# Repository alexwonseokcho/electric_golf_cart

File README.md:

# electric_golf_cart
Electric golf push cart made with hoverboard motors. Remote controlled with ESP-NOW, featuring an IMU-enabled autobalancing mode.

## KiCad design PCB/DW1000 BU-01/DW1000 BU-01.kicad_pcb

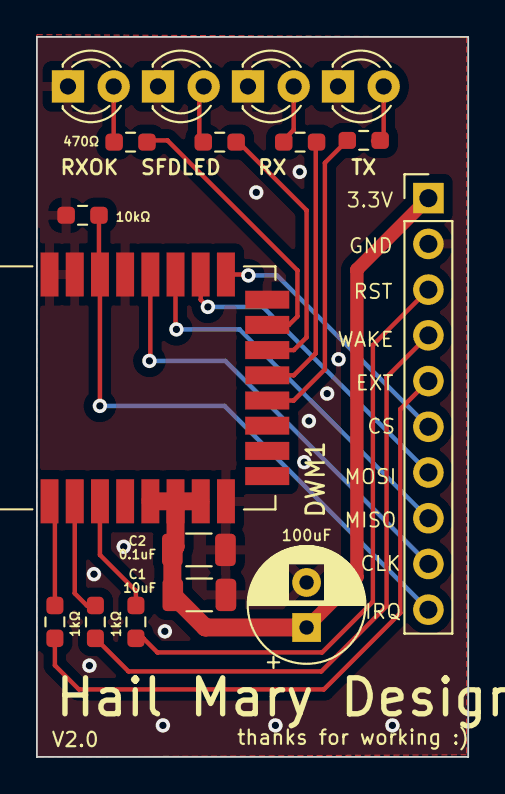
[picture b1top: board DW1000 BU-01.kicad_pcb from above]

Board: 2 copper layers, 24.0 x 40.0 mm, 17 parts (0 on the bottom side), 21 nets.

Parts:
C1: 10uF; C_1206_3216Metric
C2: 0.1uF; C_1206_3216Metric
C3: 100uF; CP_Radial_D6.3mm_P2.50mm
D1: RXOK; LED_D3.0mm
D2: SFDLED; LED_D3.0mm
D3: RX; LED_D3.0mm
D4: TX; LED_D3.0mm
DWM1: DWM1000
J1: Conn_01x10_Pin; PinHeader_1x10_P2.54mm_Vertical
R1, R2, R3, R4: R470; R_0603_1608Metric_Pad0.98x0.95mm_HandSolder
R5: R10k; R_0603_1608Metric_Pad0.98x0.95mm_HandSolder
R6, R7, R8: R1k; R_0603_1608Metric_Pad0.98x0.95mm_HandSolder

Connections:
+3.3V: C1.1, C2.1, C3.1, DWM1.5 (VDDAON), DWM1.6 (VDD3V3), DWM1.7 (VDD3V3), J1.1
EXTON: DWM1.1 (EXTON), R6.1
GND: C1.2, C2.2, C3.2, D1.1 (K), D2.1 (K), D3.1 (K), D4.1 (K), DWM1.8 (VSS), DWM1.16 (VSS), DWM1.21 (VSS), DWM1.23 (VSS), DWM1.24 (VSS), J1.2, R5.2
unnamed: D1.2 (A), R1.2
unnamed: D2.2 (A), R2.2
unnamed: D3.2 (A), R3.2
unnamed: D4.2 (A), R4.2
unnamed: DWM1.15 (GPIO0/RXOKLED), R1.1
unnamed: DWM1.14 (GPIO1/SFDLED), R2.1
unnamed: DWM1.13 (GPIO2/RXLED), R3.1
unnamed: DWM1.12 (GPIO3/TXLED), R4.1
unnamed: DWM1.22 (IRQ/GPIO8), J1.10, R5.1
unnamed: DWM1.20 (SPICLK), J1.9
unnamed: DWM1.17 (SPICSn), J1.6
unnamed: DWM1.19 (SPIMISO), J1.8
unnamed: DWM1.18 (SPIMOSI), J1.7
unnamed: J1.3, R8.2
unnamed: J1.4, R7.2
unnamed: J1.5, R6.2
RSTn: DWM1.3 (RSTn), R8.1
WAKEUP: DWM1.2 (WAKEUP), R7.1

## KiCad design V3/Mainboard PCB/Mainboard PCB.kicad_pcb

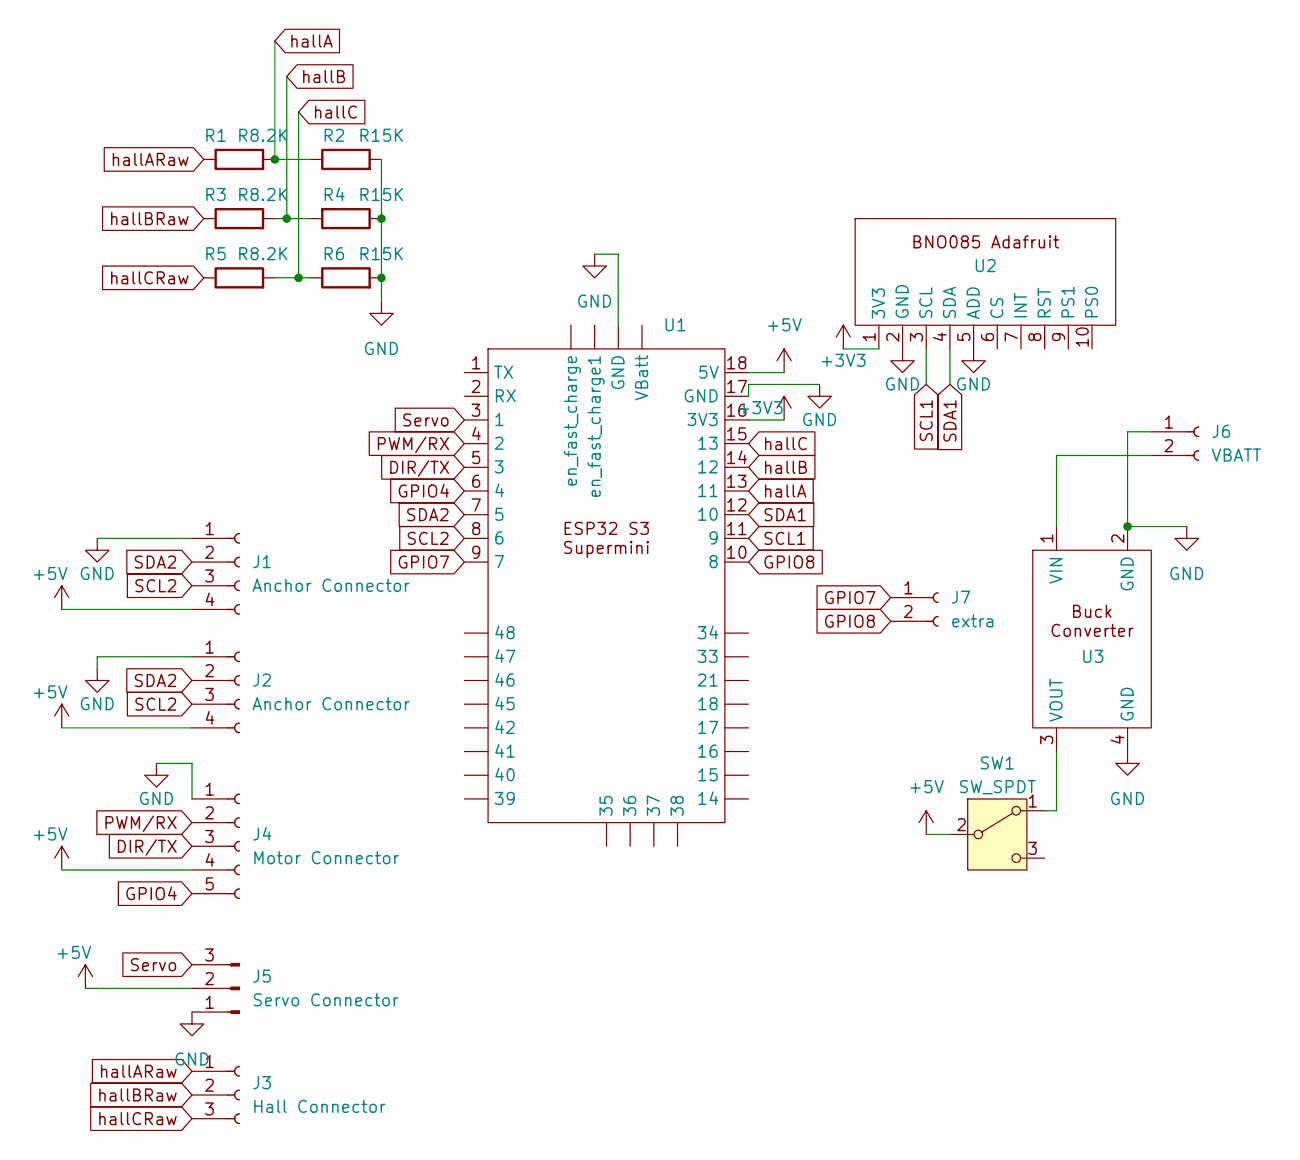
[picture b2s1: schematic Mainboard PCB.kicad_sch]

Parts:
J1, J2: Anchor Connector; PinSocket_1x04_P2.54mm_Vertical
J3: Hall Connector; PinSocket_1x03_P2.54mm_Vertical
J4: Motor Connector; PinSocket_1x05_P2.54mm_Vertical
J5: Servo Connector; PinSocket_1x03_P2.54mm_Vertical
J6: VBATT; PinSocket_1x02_P2.54mm_Vertical
J7: extra; PinSocket_1x02_P2.54mm_Vertical
R1, R3, R5: R8.2K; R_0603_1608Metric_Pad0.98x0.95mm_HandSolder
R2, R4, R6: R15K; R_0603_1608Metric_Pad0.98x0.95mm_HandSolder
SW1: SW_SPDT; Slide Switch
U1: ESP32 S3 Supermini Pinned
U2: BNO085
U3: Buck Converter

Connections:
+3V3: U1.16 (3V3), U2.1 (3V3)
+5V: J1.4, J2.4, J4.4, J5.2, SW1.2 (B), U1.18 (5V)
DIR/TX: J4.3, U1.5 (3)
GND: J1.1, J2.1, J4.1, J5.1, J6.1, R2.2, R4.1, R6.2, U1. (14), U1.17 (GND), U2.2 (GND), U2.5 (ADD), U3.2 (GND), U3.4 (GND)
GPIO4: J4.5, U1.6 (4)
GPIO7: J7.1, U1.9 (7)
GPIO8: J7.2, U1.10 (8)
unnamed: J6.2, U3.1 (VIN)
unnamed: SW1.1 (A), U3.3 (VOUT)
PWM/RX: J4.2, U1.4 (2)
SCL1: U1.11 (9), U2.3 (SCL)
SCL2: J1.3, J2.3, U1.8 (6)
SDA1: U1.12 (10), U2.4 (SDA)
SDA2: J1.2, J2.2, U1.7 (5)
Servo: J5.3, U1.3 (1)
hallA: R1.2, R2.1, U1.13 (11)
hallARaw: J3.1, R1.1
hallB: R3.2, R4.2, U1.14 (12)
hallBRaw: J3.2, R3.1
hallC: R5.2, R6.1, U1.15 (13)
hallCRaw: J3.3, R5.1

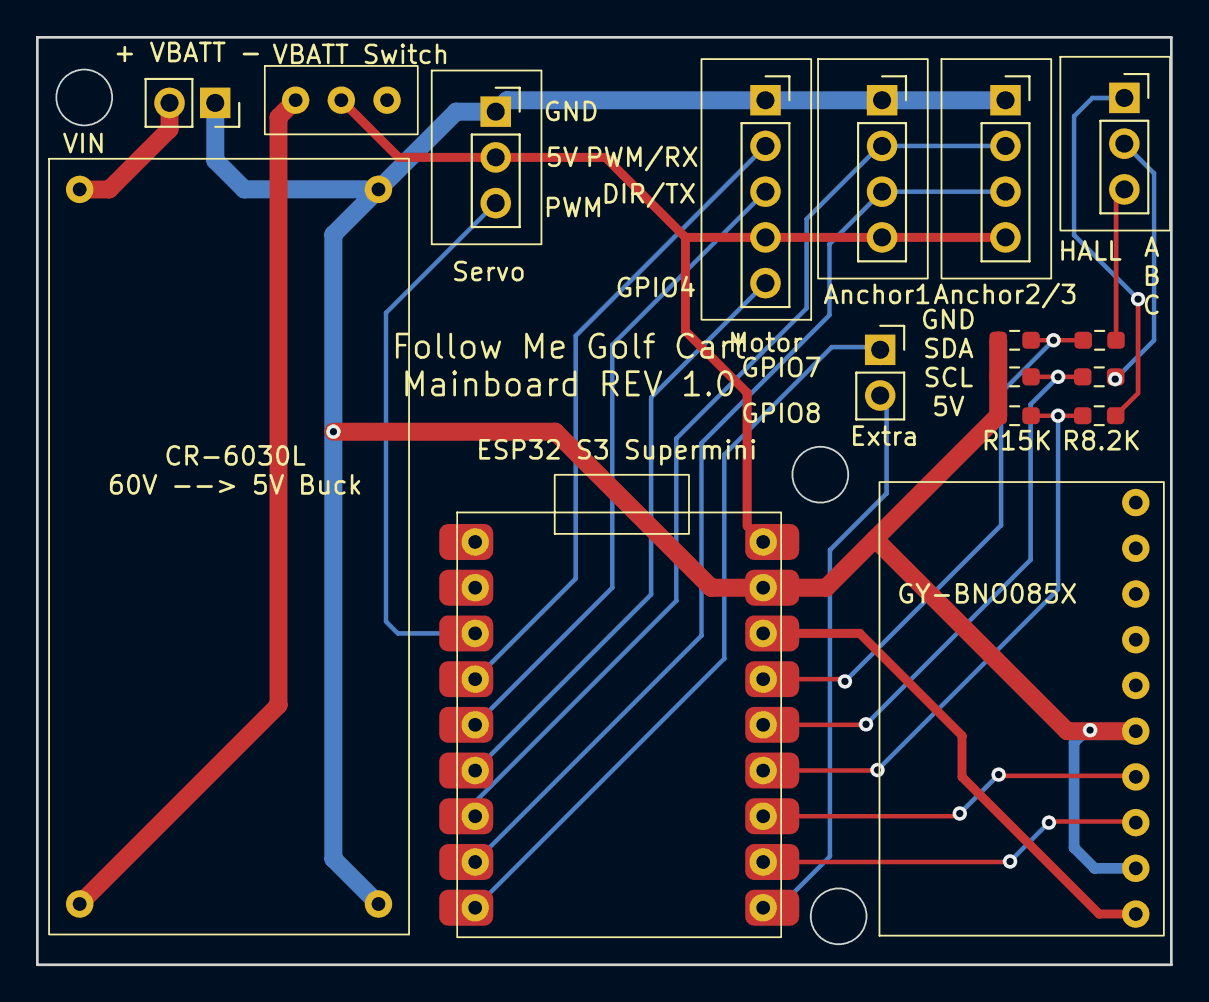
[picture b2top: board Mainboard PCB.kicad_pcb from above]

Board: 2 copper layers, 63.0 x 51.5 mm, 17 parts (0 on the bottom side), 21 nets.

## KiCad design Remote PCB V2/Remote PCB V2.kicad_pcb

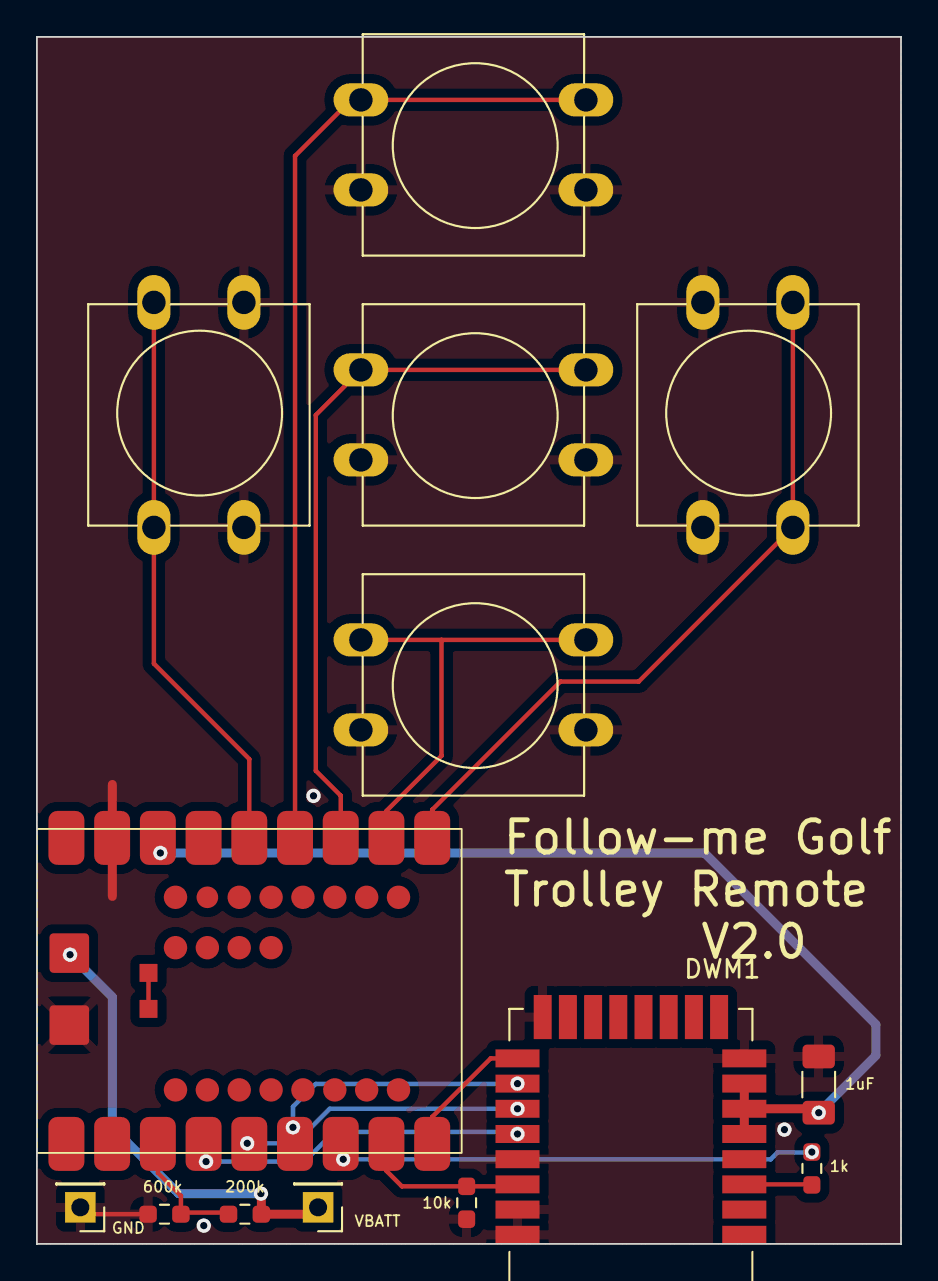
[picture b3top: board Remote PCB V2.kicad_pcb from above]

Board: 2 copper layers, 48.0 x 67.1 mm, 14 parts (0 on the bottom side), 17 nets.

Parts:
C2: 1uF; C_1206_3216Metric_Pad1.33x1.80mm_HandSolder
DWM1: DWM1000
GND: Batt Conn; PinHeader_1x01_P2.54mm_Vertical
R1: R1k; R_0603_1608Metric_Pad0.98x0.95mm_HandSolder
R2: R200k; R_0603_1608Metric_Pad0.98x0.95mm_HandSolder
R3: R680k; R_0603_1608Metric_Pad0.98x0.95mm_HandSolder
R4: R10k; R_0603_1608Metric_Pad0.98x0.95mm_HandSolder
SW1, SW2, SW3, SW4, SW5: SW_Push; SW_PUSH-12mm
U2: ESP32 S3 Supermini
VBATT1: Batt Conn; PinHeader_1x01_P2.54mm_Vertical

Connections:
+3V3: C2.2, DWM1.5 (VDDAON), DWM1.6 (VDD3V3), DWM1.7 (VDD3V3), U2.16 (3V3)
CLK: DWM1.20 (SPICLK), U2.4 (2)
CS: DWM1.17 (SPICSn), U2.9 (7)
DOWN: SW4.1, U2.11 (9)
GND: C2.1, DWM1.8 (VSS), DWM1.16 (VSS), DWM1.21 (VSS), DWM1.23 (VSS), DWM1.24 (VSS), GND.1, R3.2, R4.2, SW1.2, SW2.2, SW3.2, SW4.2, SW5.1, U2.17 (GND), U2.19 (GND)
IRQ: DWM1.22 (IRQ/GPIO8), R4.1, U2.8 (6)
LEFT: SW1.1, U2.14 (12)
MISO: DWM1.19 (SPIMISO), U2.5 (3)
MOSI: DWM1.18 (SPIMOSI), U2.6 (4)
unnamed: DWM1.3 (RSTn), R1.1
unnamed: U2.21 (en_fast_charge1), U2.22 (en_fast_charge)
RIGHT: SW5.2, U2.10 (8)
RST: R1.2, U2.7 (5)
STOP: SW3.1, U2.12 (10)
UP: SW2.1, U2.13 (11)
VBATT: R2.1, U2.20 (VBatt), VBATT1.1
VBATT_DIV: R2.2, R3.1, U2.3 (1)

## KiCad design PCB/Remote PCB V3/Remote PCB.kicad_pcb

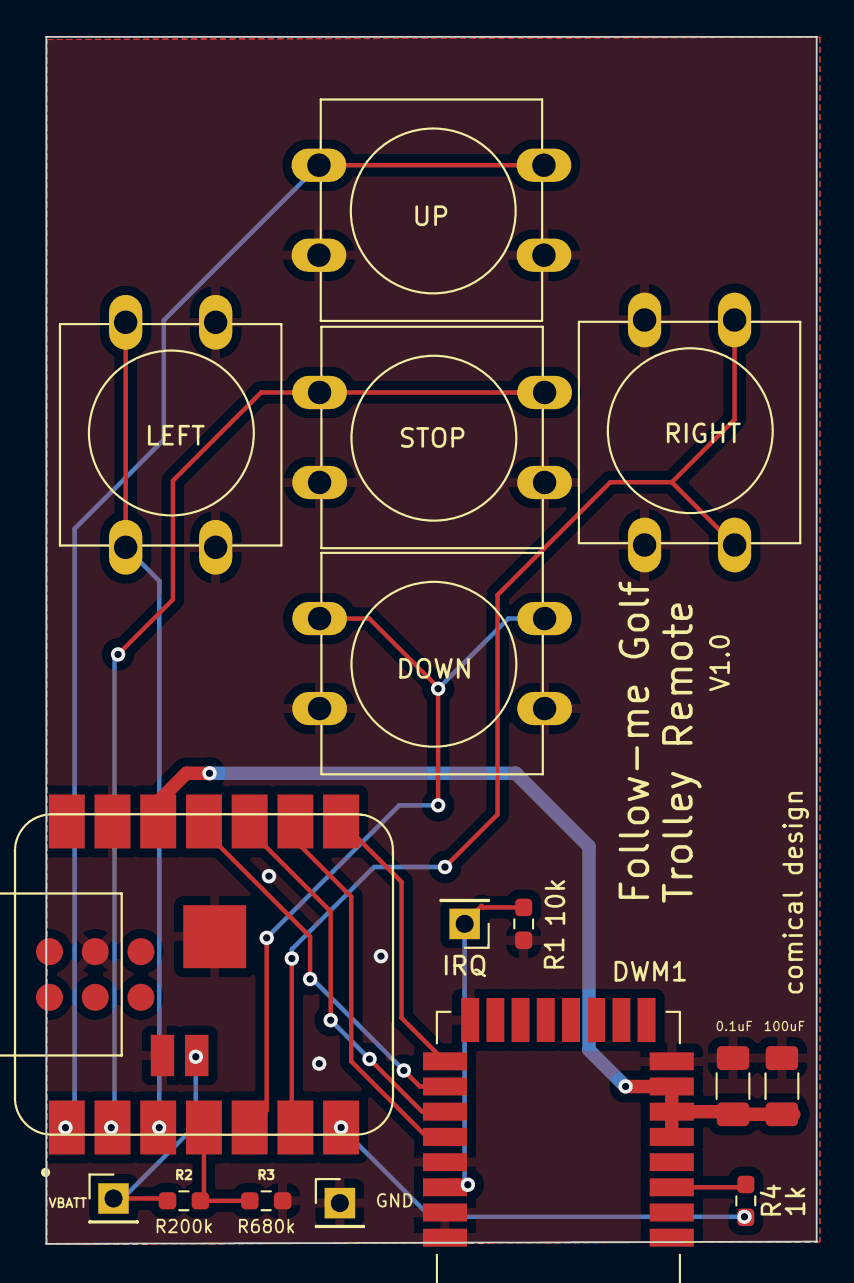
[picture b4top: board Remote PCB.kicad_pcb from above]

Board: 2 copper layers, 42.8 x 67.1 mm, 16 parts (0 on the bottom side), 16 nets.

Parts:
C1: 1uF; C_1206_3216Metric_Pad1.33x1.80mm_HandSolder
C2: 100uF; C_1206_3216Metric_Pad1.33x1.80mm_HandSolder
DWM1: DWM1000
GND: Batt Conn; PinHeader_1x01_P2.54mm_Vertical
IRQ: IRQ Test Point; PinHeader_1x01_P2.54mm_Vertical
R1: R10k; R_0603_1608Metric_Pad0.98x0.95mm_HandSolder
R2: R200k; R_0603_1608Metric_Pad0.98x0.95mm_HandSolder
R3: R680k; R_0603_1608Metric_Pad0.98x0.95mm_HandSolder
R4: R1k; R_0603_1608Metric_Pad0.98x0.95mm_HandSolder
SW1, SW2, SW3, SW4, SW5: SW_Push; SW_PUSH-12mm
U1: XIAO ESP32C3; XIAO-ESP32C3-14P-2.54-21X17.8MM
VBATT: Batt Conn; PinHeader_1x01_P2.54mm_Vertical

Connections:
+3V3: C1.2, C2.2, DWM1.5 (VDDAON), DWM1.6 (VDD3V3), DWM1.7 (VDD3V3), U1.12 (3V3)
CLK: DWM1.20 (SPICLK), U1.9 (PA7_A8_D8_SCK)
CS: DWM1.17 (SPICSn), U1.8 (PB09_A7_D7_RX)
DOWN: SW3.1, U1.5 (PA8_A4_D4_SDA)
GND: C1.1, C2.1, DWM1.8 (VSS), DWM1.16 (VSS), DWM1.21 (VSS), DWM1.23 (VSS), DWM1.24 (VSS), GND.1, R1.2, R3.2, SW1.2, SW2.2, SW3.2, SW4.2, SW5.1, U1.13 (GND), U1.18 (GND), U1.21 (GND), U1.23 (GND)
IRQ: DWM1.22 (IRQ/GPIO8), IRQ.1, R1.1
LEFT: SW4.1, U1.3 (PA10_A2_D2)
MISO: DWM1.19 (SPIMISO), U1.10 (PA5_A9_D9_MISO)
MOSI: DWM1.18 (SPIMOSI), U1.11 (PA6_A10_D10_MOSI)
unnamed: DWM1.3 (RSTn), R4.1
RIGHT: SW5.2, U1.6 (PA9_A5_D5_SCL)
RST: R4.2, U1.7 (PB08_A6_D6_TX)
STOP: SW2.1, U1.2 (PA4_A1_D1)
UP: SW1.1, U1.1 (PA02_A0_D0)
VBATT: R2.1, U1.22 (VBatt), VBATT.1
VBATT_DIV: R2.2, R3.1, U1.4 (PA11_A3_D3)

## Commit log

2024-03-07 added PCB for DW1000 dev
2024-03-07 esp32 espnow based transmission
2024-03-07 Added initial display config & test code
2024-05-07 cart remote pcb v2 update and follow me initial code
2024-07-10 v3 remote code changes
2024-08-19 so many changes ahaha... Remote V2 architecture overhaul, V3 with front wheel drive, and freertos receiver side software overhaul. Odrive initial tests with UART
2024-08-19 misc
2024-11-07 V4 with more concrete UWB follow code using only 2 anchors
2024-11-08 localization visualization code
2024-11-08 added particle filter
